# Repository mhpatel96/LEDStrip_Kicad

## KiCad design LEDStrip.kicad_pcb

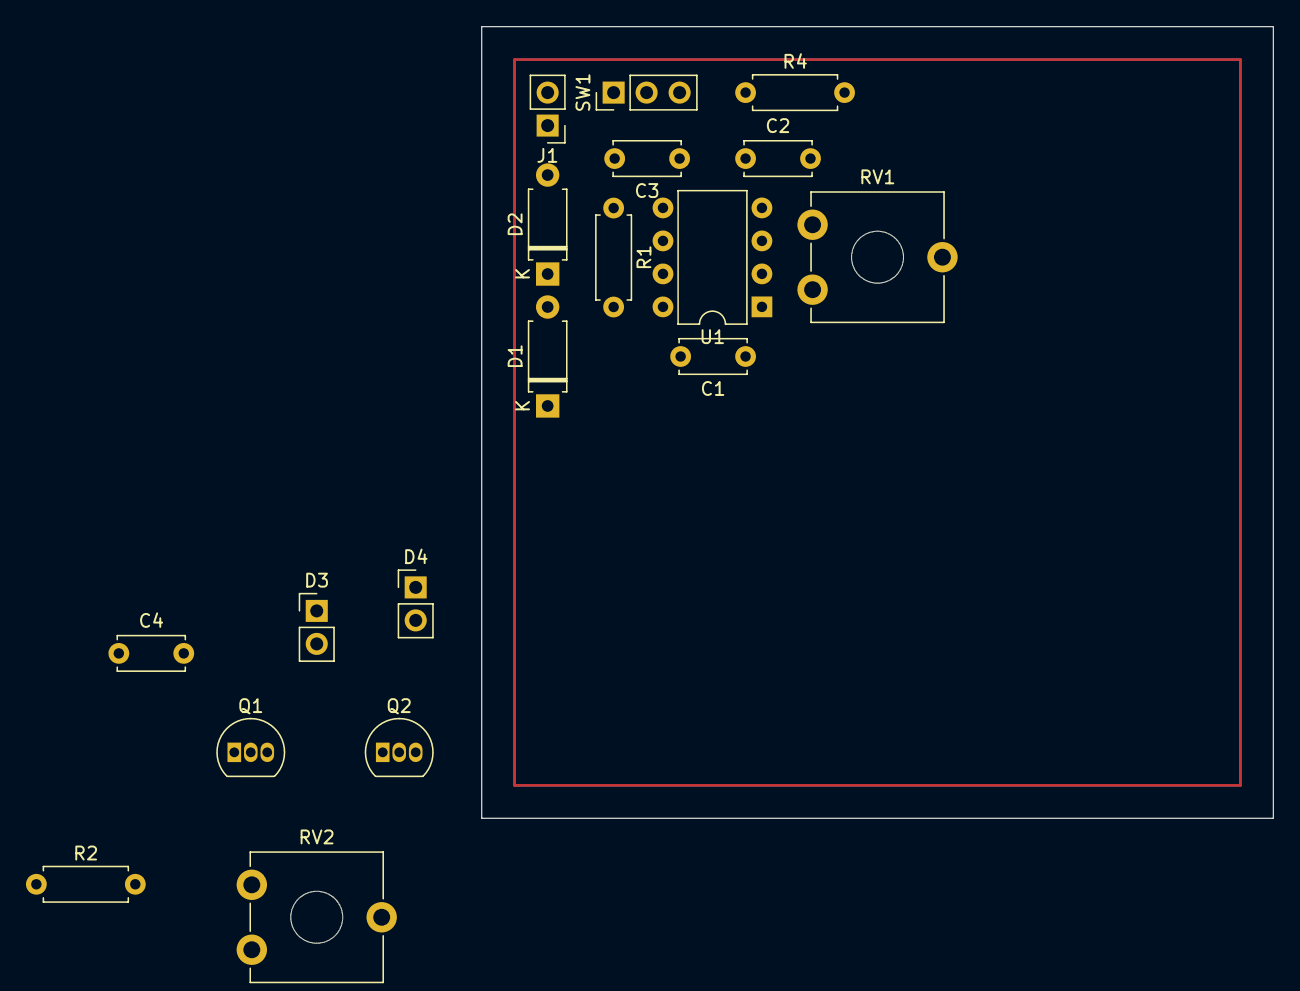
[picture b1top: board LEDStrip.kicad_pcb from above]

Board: 2 copper layers, 61.0 x 61.0 mm, 18 parts (0 on the bottom side), 13 nets, no tracks yet.

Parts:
C1: 1n; C_Disc_D5.0mm_W2.5mm_P5.00mm
C2, C3, C4: 100n; C_Disc_D5.0mm_W2.5mm_P5.00mm
D1, D2: DIODE; D_A-405_P7.62mm_Horizontal
D3, D4: LED_AGBR; PinHeader_1x02_P2.54mm_Vertical
J1: Conn_01x02; PinHeader_1x02_P2.54mm_Vertical
Q1: BC517; TO-92_Inline
Q2: BC516; TO-92_Inline
R1, R4: 10k; R_Axial_DIN0207_L6.3mm_D2.5mm_P7.62mm_Horizontal
R2: 240k; R_Axial_DIN0207_L6.3mm_D2.5mm_P7.62mm_Horizontal
RV1: 10k; Potentiometer_ACP_CA9-V10_Vertical_Hole
RV2: 220k; Potentiometer_ACP_CA9-V10_Vertical_Hole
SW1: SW_SPST; PinHeader_1x03_P2.54mm_Vertical
U1: LM555xN; DIP-8_W7.62mm

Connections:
+12V: C3.1, C4.1, D3.1 (A), D4.1 (A), R1.1, R4.1, SW1.2 (B), U1.8 (VCC)
/pwm: R2.1, U1.3 (Q)
GND: C1.2, C2.2, C3.2, C4.2, J1.1, Q1.3 (E), Q2.3 (E), U1.1 (GND)
unnamed: C1.1, RV1.2
unnamed: C2.1, R4.2, U1.4 (R)
unnamed: D1.1 (A), RV1.3
unnamed: D1.2 (K), D2.1 (A), R1.2, U1.7 (DIS)
unnamed: D2.2 (K), RV1.1, U1.2 (TR), U1.6 (THR)
unnamed: D3.2 (GK), Q1.1 (C)
unnamed: D4.2 (GK), Q2.1 (C)
unnamed: J1.2, SW1.1 (A)
unnamed: Q1.2 (B), Q2.2 (B), RV2.2, RV2.3
unnamed: R2.2, RV2.1

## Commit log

2023-02-10 -Added group brightness control
